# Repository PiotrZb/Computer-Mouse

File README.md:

# Computer Mouse project 🖱️

## Description 📜

Educational computer mouse project created in KiCad. The project includes an electrical schematic, PCB schematic and Gerber production files.

## Contributors 🤝

<div style="display: flex;">
     
</div>

## License 📄

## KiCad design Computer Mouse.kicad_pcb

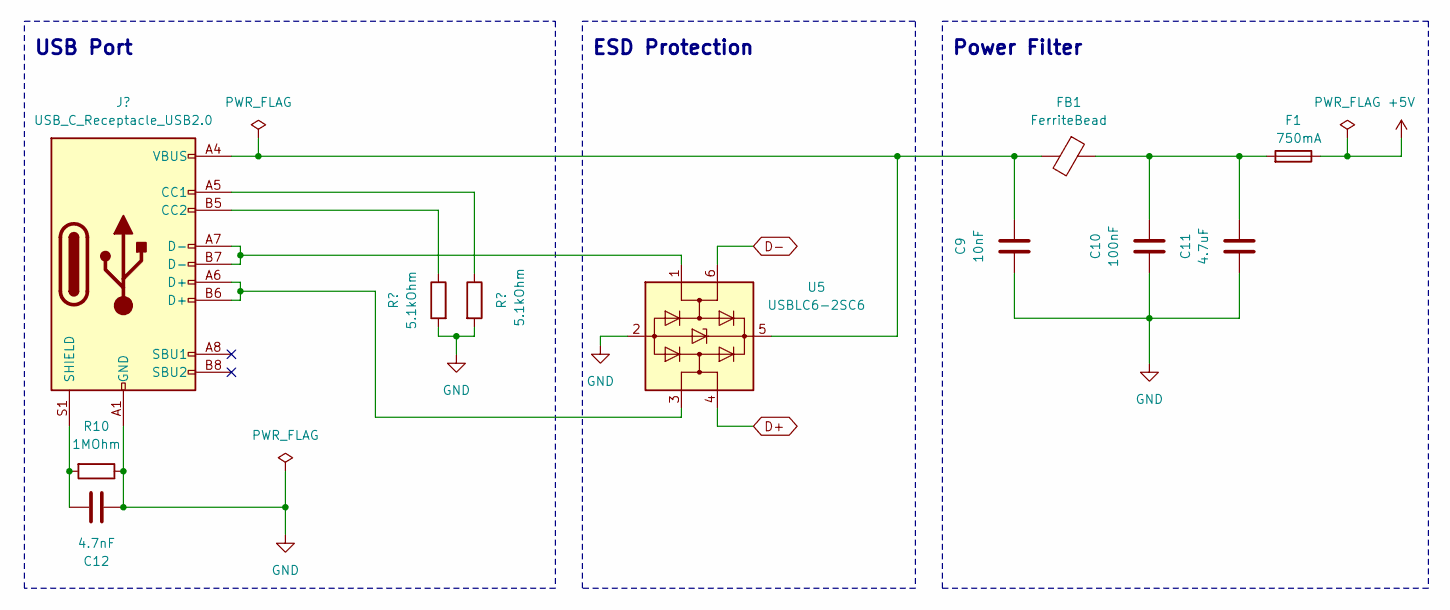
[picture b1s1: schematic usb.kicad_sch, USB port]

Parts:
C9: 10nF; C_0603_1608Metric
C10: 100nF; C_0805_2012Metric
C11: 4.7uF; C_0603_1608Metric
C12: 4.7nF; C_0805_2012Metric
F1: 750mA; Fuse_0402_1005Metric
FB1: FerriteBead; C_2220_5650Metric
J2: USB_C_Receptacle_USB2.0; USB_C_Receptacle_HRO_TYPE-C-31-M-12
R8, R9: 5.1kOhm; R_0603_1608Metric
R10: 1MOhm; R_1206_3216Metric
U5: USBLC6-2SC6; SOT-23-6

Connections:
+5V: F1.1; also elsewhere on the board
D+: U5.4 (I/O2); also elsewhere on the board
D-: U5.6 (I/O1); also elsewhere on the board
unnamed: C10.2, C11.2, F1.2, FB1.1
unnamed: J2.A5 (CC1), R9.1
unnamed: J2.B5 (CC2), R8.1
unnamed: J2.A6 (D+), J2.B6 (D+), U5.3 (I/O2)
unnamed: J2.A7 (D-), J2.B7 (D-), U5.1 (I/O1)
unnamed: C12.2, J2.S1 (SHIELD), R10.2
unnamed: C9.2, FB1.2, J2.A4 (VBUS), J2.A9 (VBUS), J2.B4 (VBUS), J2.B9 (VBUS), U5.5 (VBUS)

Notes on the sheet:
Power Filter
ESD Protection
USB Port

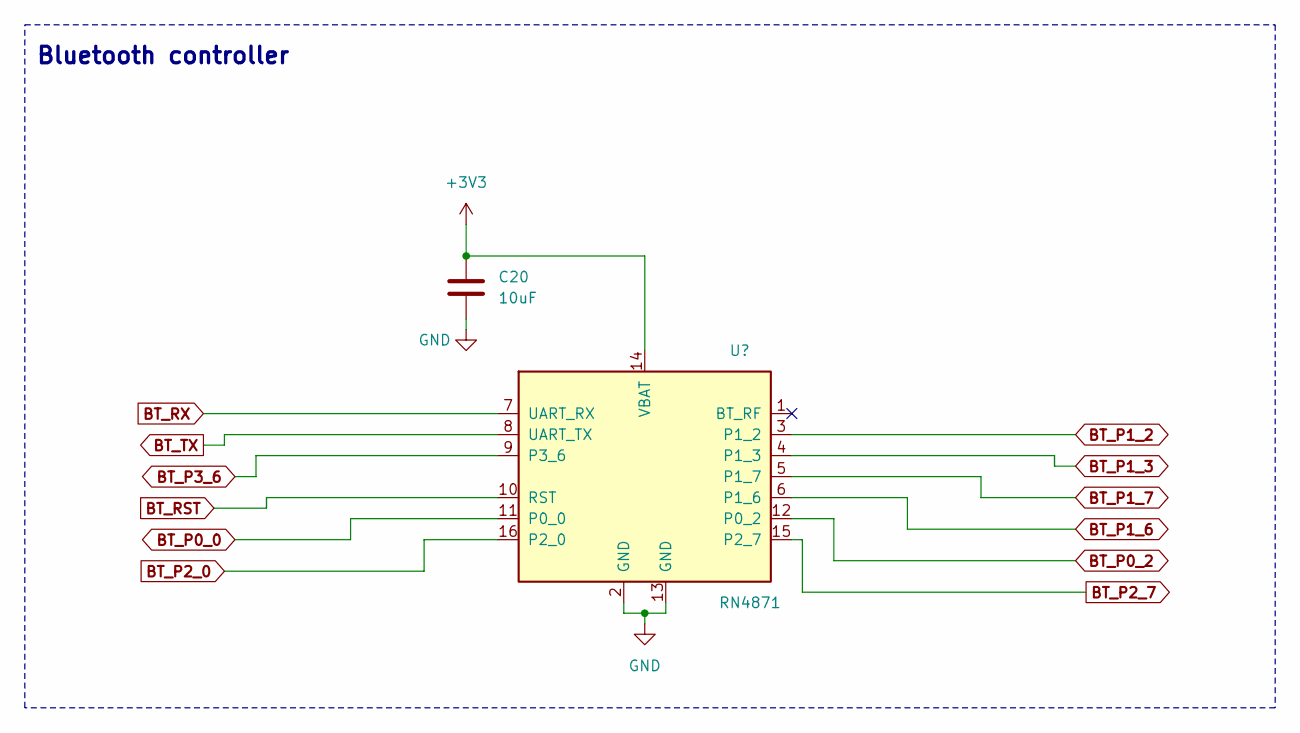
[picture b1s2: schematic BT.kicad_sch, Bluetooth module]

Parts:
C20: 10uF; C_1206_3216Metric
U10: RN4871; Microchip_RN4871

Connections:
BT_P0_0: U10.11 (P0_0); also elsewhere on the board
BT_P0_2: U10.12 (P0_2); also elsewhere on the board
BT_P1_2: U10.3 (P1_2); also elsewhere on the board
BT_P1_3: U10.4 (P1_3); also elsewhere on the board
BT_P1_6: U10.6 (P1_6); also elsewhere on the board
BT_P1_7: U10.5 (P1_7); also elsewhere on the board
BT_P2_0: U10.16 (P2_0); also elsewhere on the board
BT_P2_7: U10.15 (P2_7); also elsewhere on the board
BT_P3_6: U10.9 (P3_6); also elsewhere on the board
BT_RST: U10.10 (RST); also elsewhere on the board
BT_RX: U10.7 (UART_RX); also elsewhere on the board
BT_TX: U10.8 (UART_TX); also elsewhere on the board

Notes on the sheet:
Bluetooth controller

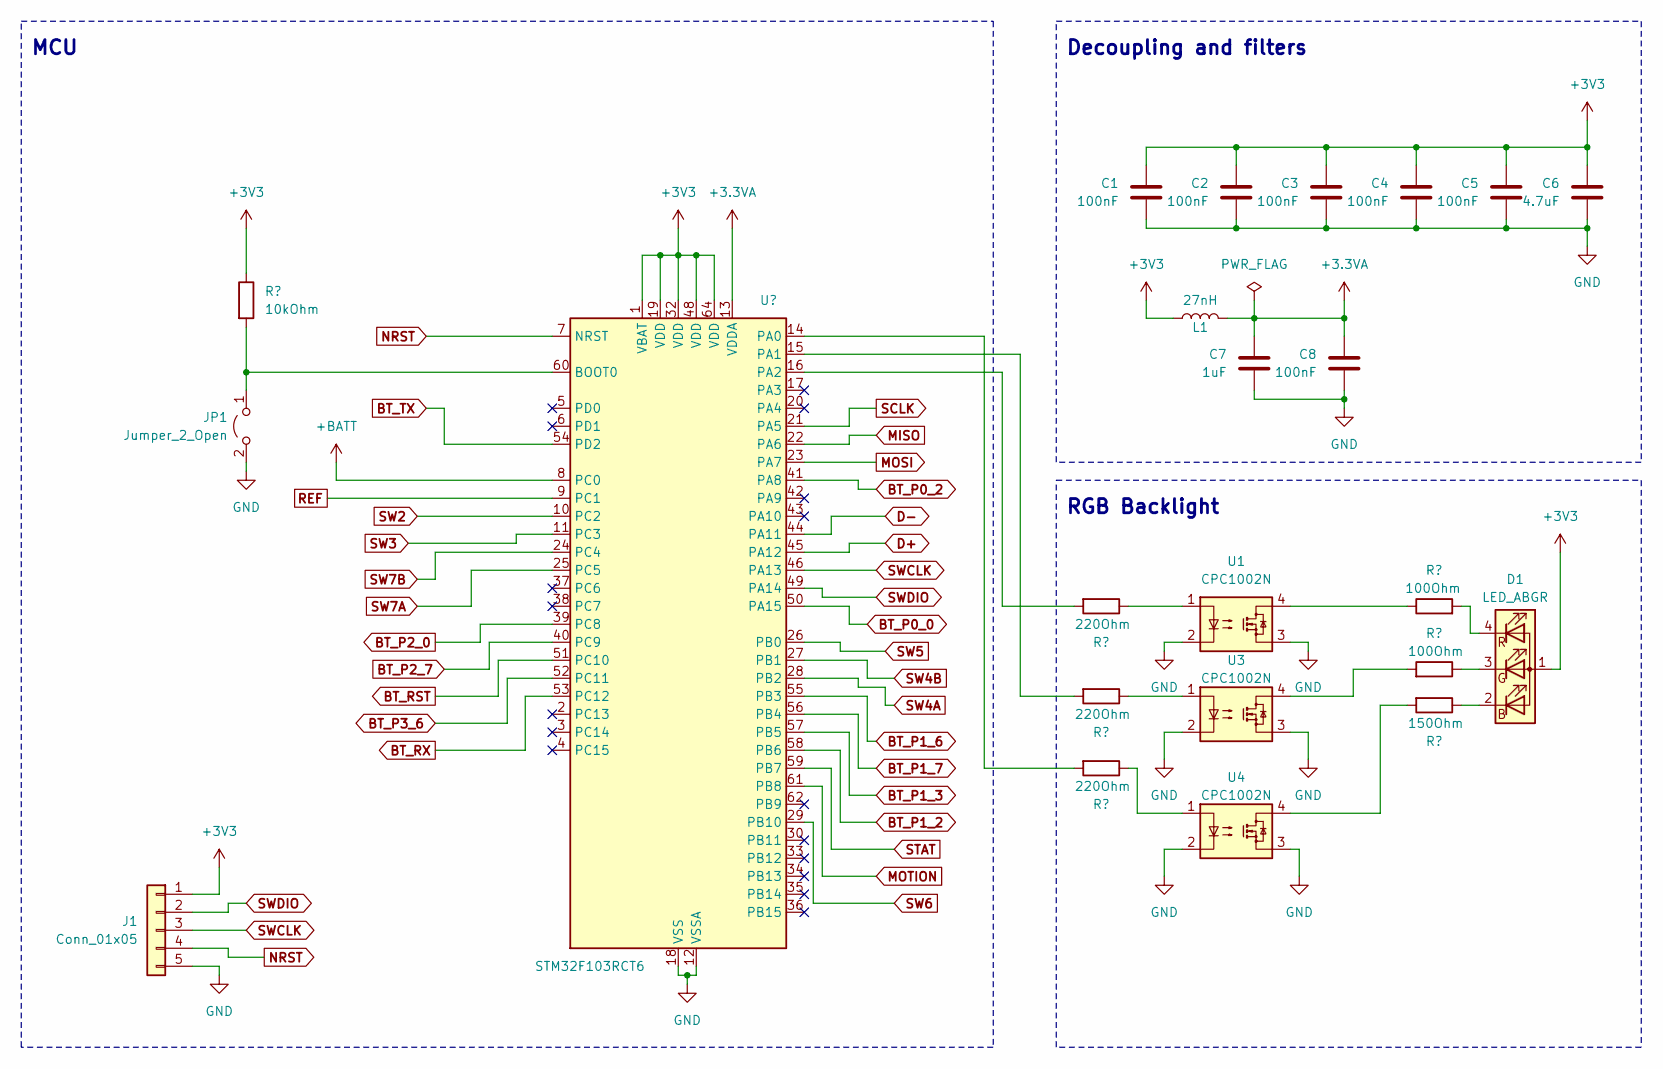
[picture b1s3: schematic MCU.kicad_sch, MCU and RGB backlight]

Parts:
C1, C2, C3, C4, C5, C8: 100nF; C_0805_2012Metric
C6: 4.7uF; C_0603_1608Metric
C7: 1uF; C_0603_1608Metric
D1: LED_ABGR; LED_D5.0mm-4_RGB_Wide_Pins
J1: Conn_01x05; JST_EH_B5B-EH-A_1x05_P2.50mm_Vertical
JP1: Jumper_2_Open; SolderJumper-2_P1.3mm_Bridged2Bar_Pad1.0x1.5mm
L1: 27nH; L_1210_3225Metric
R1: 10kOhm; R_0805_2012Metric
R2, R5, R7: 220Ohm; R_1206_3216Metric
R3, R4: 100Ohm; R_0805_2012Metric
R6: 150Ohm; R_1206_3216Metric
U1, U3, U4: CPC1002N; SOP-4_3.8x4.1mm_P2.54mm
U2: STM32F103RCT6; LQFP-64_10x10mm_P0.5mm

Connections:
+3.3VA: C7.1, C8.1, L1.1, U2.13 (VDDA)
+BATT: U2.8 (PC0); also elsewhere on the board
BT_P0_0: U2.50 (PA15); also elsewhere on the board
BT_P0_2: U2.41 (PA8); also elsewhere on the board
BT_P1_2: U2.58 (PB6); also elsewhere on the board
BT_P1_3: U2.57 (PB5); also elsewhere on the board
BT_P1_6: U2.55 (PB3); also elsewhere on the board
BT_P1_7: U2.56 (PB4); also elsewhere on the board
BT_P2_0: U2.39 (PC8); also elsewhere on the board
BT_P2_7: U2.40 (PC9); also elsewhere on the board
BT_P3_6: U2.52 (PC11); also elsewhere on the board
BT_RST: U2.51 (PC10); also elsewhere on the board
BT_RX: U2.53 (PC12); also elsewhere on the board
BT_TX: U2.54 (PD2); also elsewhere on the board
D+: U2.45 (PA12); also elsewhere on the board
D-: U2.44 (PA11); also elsewhere on the board
MISO: U2.22 (PA6); also elsewhere on the board
MOSI: U2.23 (PA7); also elsewhere on the board
MOTION: U2.61 (PB8); also elsewhere on the board
NRST: J1.4, U2.7 (NRST)
unnamed: D1.2 (BK), R6.1
unnamed: D1.3 (GK), R4.1
unnamed: D1.4 (RK), R3.2
unnamed: JP1.1 (A), R1.2, U2.60 (BOOT0)
unnamed: R3.1, U1.4
unnamed: R4.2, U3.4
unnamed: R5.1, U3.1
unnamed: R6.2, U4.4
unnamed: R7.1, U4.1
unnamed: R7.2, U2.14 (PA0)
unnamed: R5.2, U2.15 (PA1)
REF: U2.9 (PC1); also elsewhere on the board
STAT: U2.59 (PB7); also elsewhere on the board
SW2: U2.10 (PC2); also elsewhere on the board
SW3: U2.11 (PC3); also elsewhere on the board
SW4A: U2.28 (PB2); also elsewhere on the board
SW4B: U2.27 (PB1); also elsewhere on the board
SW5: U2.26 (PB0); also elsewhere on the board
SW6: U2.29 (PB10); also elsewhere on the board
SW7A: U2.25 (PC5); also elsewhere on the board
SW7B: U2.24 (PC4); also elsewhere on the board
SWCLK: J1.3, U2.46 (PA13)
SWDIO: J1.2, U2.49 (PA14)

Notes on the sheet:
Decoupling and filters
RGB Backlight
MCU

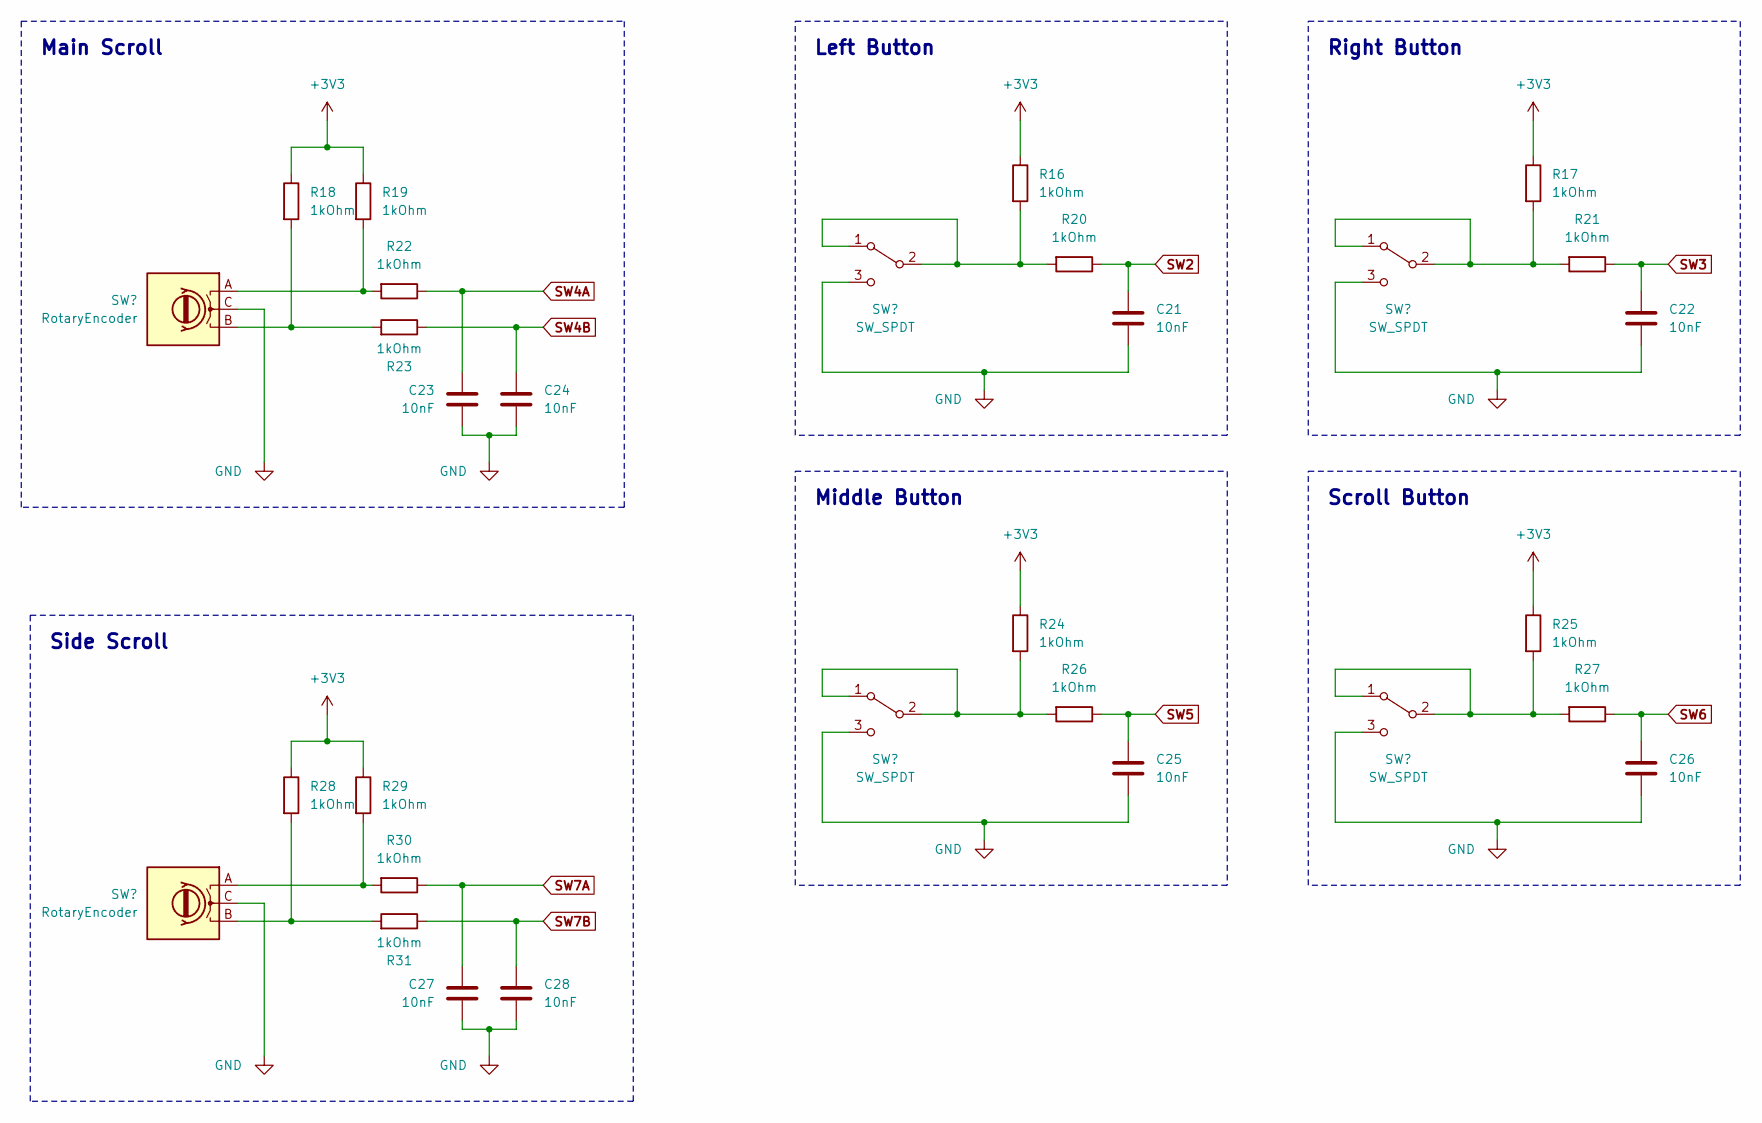
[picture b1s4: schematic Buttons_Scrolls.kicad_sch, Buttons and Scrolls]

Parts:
C21, C22, C23, C24, C25, C26, C27, C28: 10nF; C_0603_1608Metric
R16, R17, R18, R19, R20, R21, R22, R23, R24, R25, R26, R27, R28, R29, R30, R31: 1kOhm; R_0603_1608Metric
SW2, SW3, SW5, SW6: SW_SPDT; Mouse_Switch
SW4, SW7: RotaryEncoder; TTC_rotary_encoder

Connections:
unnamed: R18.2, R23.2, SW4.B
unnamed: R19.2, R22.2, SW4.A
unnamed: R28.2, R31.2, SW7.B
unnamed: R29.2, R30.2, SW7.A
unnamed: R16.2, R20.2, SW2.1 (A), SW2.2 (B)
unnamed: R17.2, R21.2, SW3.1 (A), SW3.2 (B)
unnamed: R24.2, R26.2, SW5.1 (A), SW5.2 (B)
unnamed: R25.2, R27.2, SW6.1 (A), SW6.2 (B)
SW2: C21.1, R20.1; also elsewhere on the board
SW3: C22.1, R21.1; also elsewhere on the board
SW4A: C23.1, R22.1; also elsewhere on the board
SW4B: C24.1, R23.1; also elsewhere on the board
SW5: C25.1, R26.1; also elsewhere on the board
SW6: C26.1, R27.1; also elsewhere on the board
SW7A: C27.1, R30.1; also elsewhere on the board
SW7B: C28.1, R31.1; also elsewhere on the board

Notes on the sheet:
Middle Button
Scroll Button
Left Button
Side Scroll
Right Button
Main Scroll

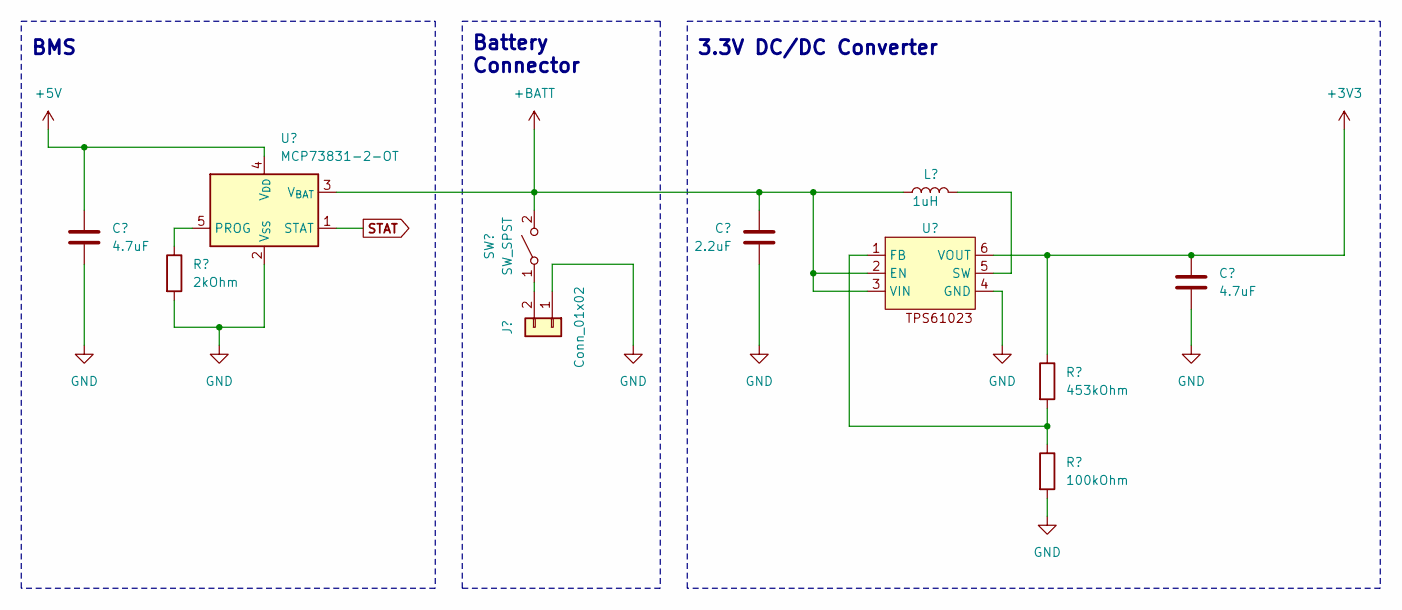
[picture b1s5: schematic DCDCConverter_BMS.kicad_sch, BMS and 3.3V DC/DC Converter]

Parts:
C13, C15: 4.7uF; C_0603_1608Metric
C14: 2.2uF; C_0805_2012Metric
J3: Conn_01x02; JST_EH_B2B-EH-A_1x02_P2.50mm_Vertical
L2: 1uH; L_0603_1608Metric_Pad1.05x0.95mm_HandSolder
R11: 2kOhm; R_0805_2012Metric
R12: 453kOhm; R_0805_2012Metric
R13: 100kOhm; R_0805_2012Metric
SW1: SW_SPST; SW_DIP_SPSTx01_Slide_6.7x4.1mm_W7.62mm_P2.54mm_LowProfile
U6: MCP73831-2-OT; SOT-23-5
U7: TPS61023_DC_DC

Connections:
+5V: C13.1, U6.4 (V_{DD}); also elsewhere on the board
+BATT: C14.1, L2.1, SW1.2 (B), U6.3 (V_{BAT}), U7.2 (EN), U7.3 (VIN); also elsewhere on the board
unnamed: J3.2, SW1.1 (A)
unnamed: R11.1, U6.5 (PROG)
unnamed: R12.2, R13.1, U7.1 (FB)
unnamed: L2.2, U7.5 (SW)
STAT: U6.1 (STAT); also elsewhere on the board

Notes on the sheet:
BMS
Battery Connector
3.3V DC/DC Converter

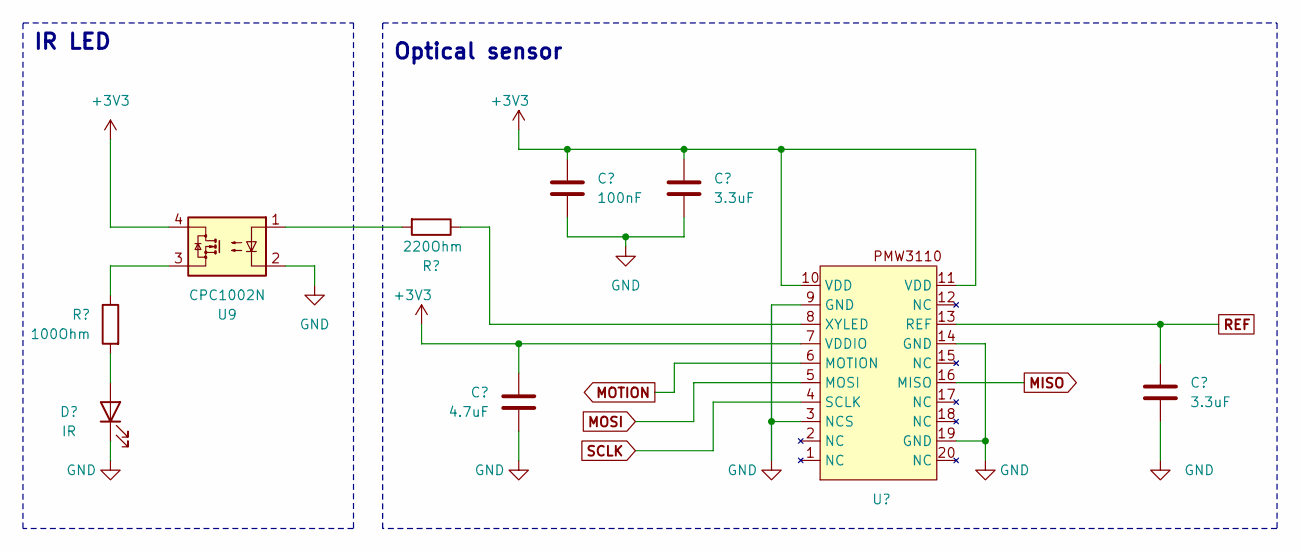
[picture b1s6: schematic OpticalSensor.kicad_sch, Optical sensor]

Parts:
C16: 100nF; C_0805_2012Metric
C17, C18: 3.3uF; C_0805_2012Metric
C19: 4.7uF; C_0603_1608Metric
D2: IR; LED_D5.0mm_Horizontal_O1.27mm_Z3.0mm_Clear
R2: 220Ohm; R_1206_3216Metric
R15: 100Ohm; R_0805_2012Metric
U9: CPC1002N; SOP-4_3.8x4.1mm_P2.54mm

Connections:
MISO: U9.16 (MISO); also elsewhere on the board
MOSI: U9.5 (MOSI); also elsewhere on the board
MOTION: U9.6 (MOTION); also elsewhere on the board
unnamed: D2.2 (A), R15.2
REF: C18.1, U9.13 (REF); also elsewhere on the board

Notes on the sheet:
IR LED
Optical sensor

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
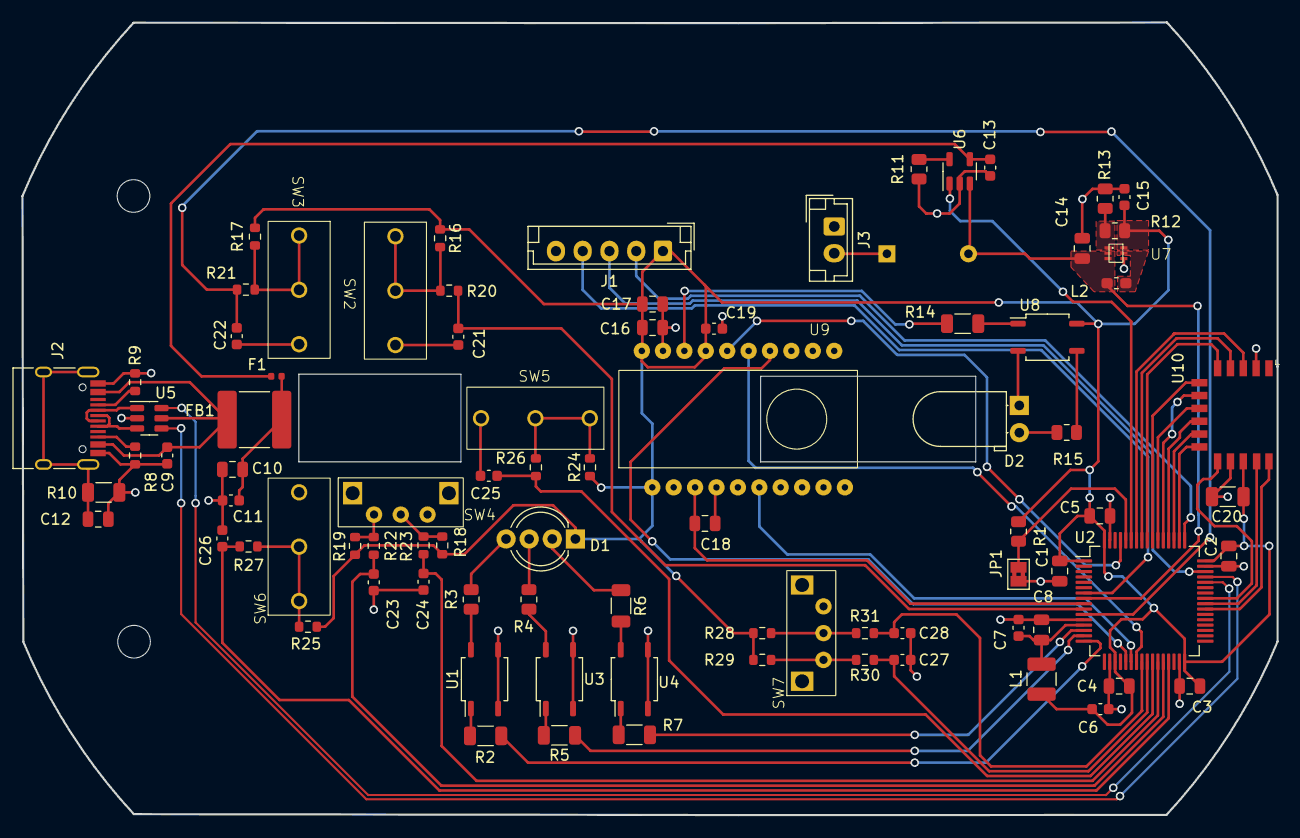
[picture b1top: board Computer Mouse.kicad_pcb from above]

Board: 2 copper layers, 117.3 x 74.1 mm, 86 parts (1 on the bottom side), 72 nets.

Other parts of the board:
R14: 220Ohm; R_1206_3216Metric
U8: CPC1002N; SOP-4_3.8x4.1mm_P2.54mm

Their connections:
unnamed: R14.2, U8.1

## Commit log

2023-11-12 BT module
2023-11-12 ERC fix
2023-11-14 New footprints
2023-11-19 New layout, pull-up resistors, filters, decoupling capacitors
2023-12-10 Arrangement of elements
2023-12-10 Board outlines
2023-12-10 MCU-BT connection
2023-12-10 Other connections
2023-12-11 Bugfixes
2024-01-02 3.3V paths, new usb module
2024-01-02 GND fields
2024-02-12 Readme update, gerber files

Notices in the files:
README.md:
License 📄:
[License: MIT](LICENSE)
